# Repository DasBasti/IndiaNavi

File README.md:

# IndiaNavi
Offline Wandernavigation mit 7-Farben ePaper Display

## PCB
Board Version 2

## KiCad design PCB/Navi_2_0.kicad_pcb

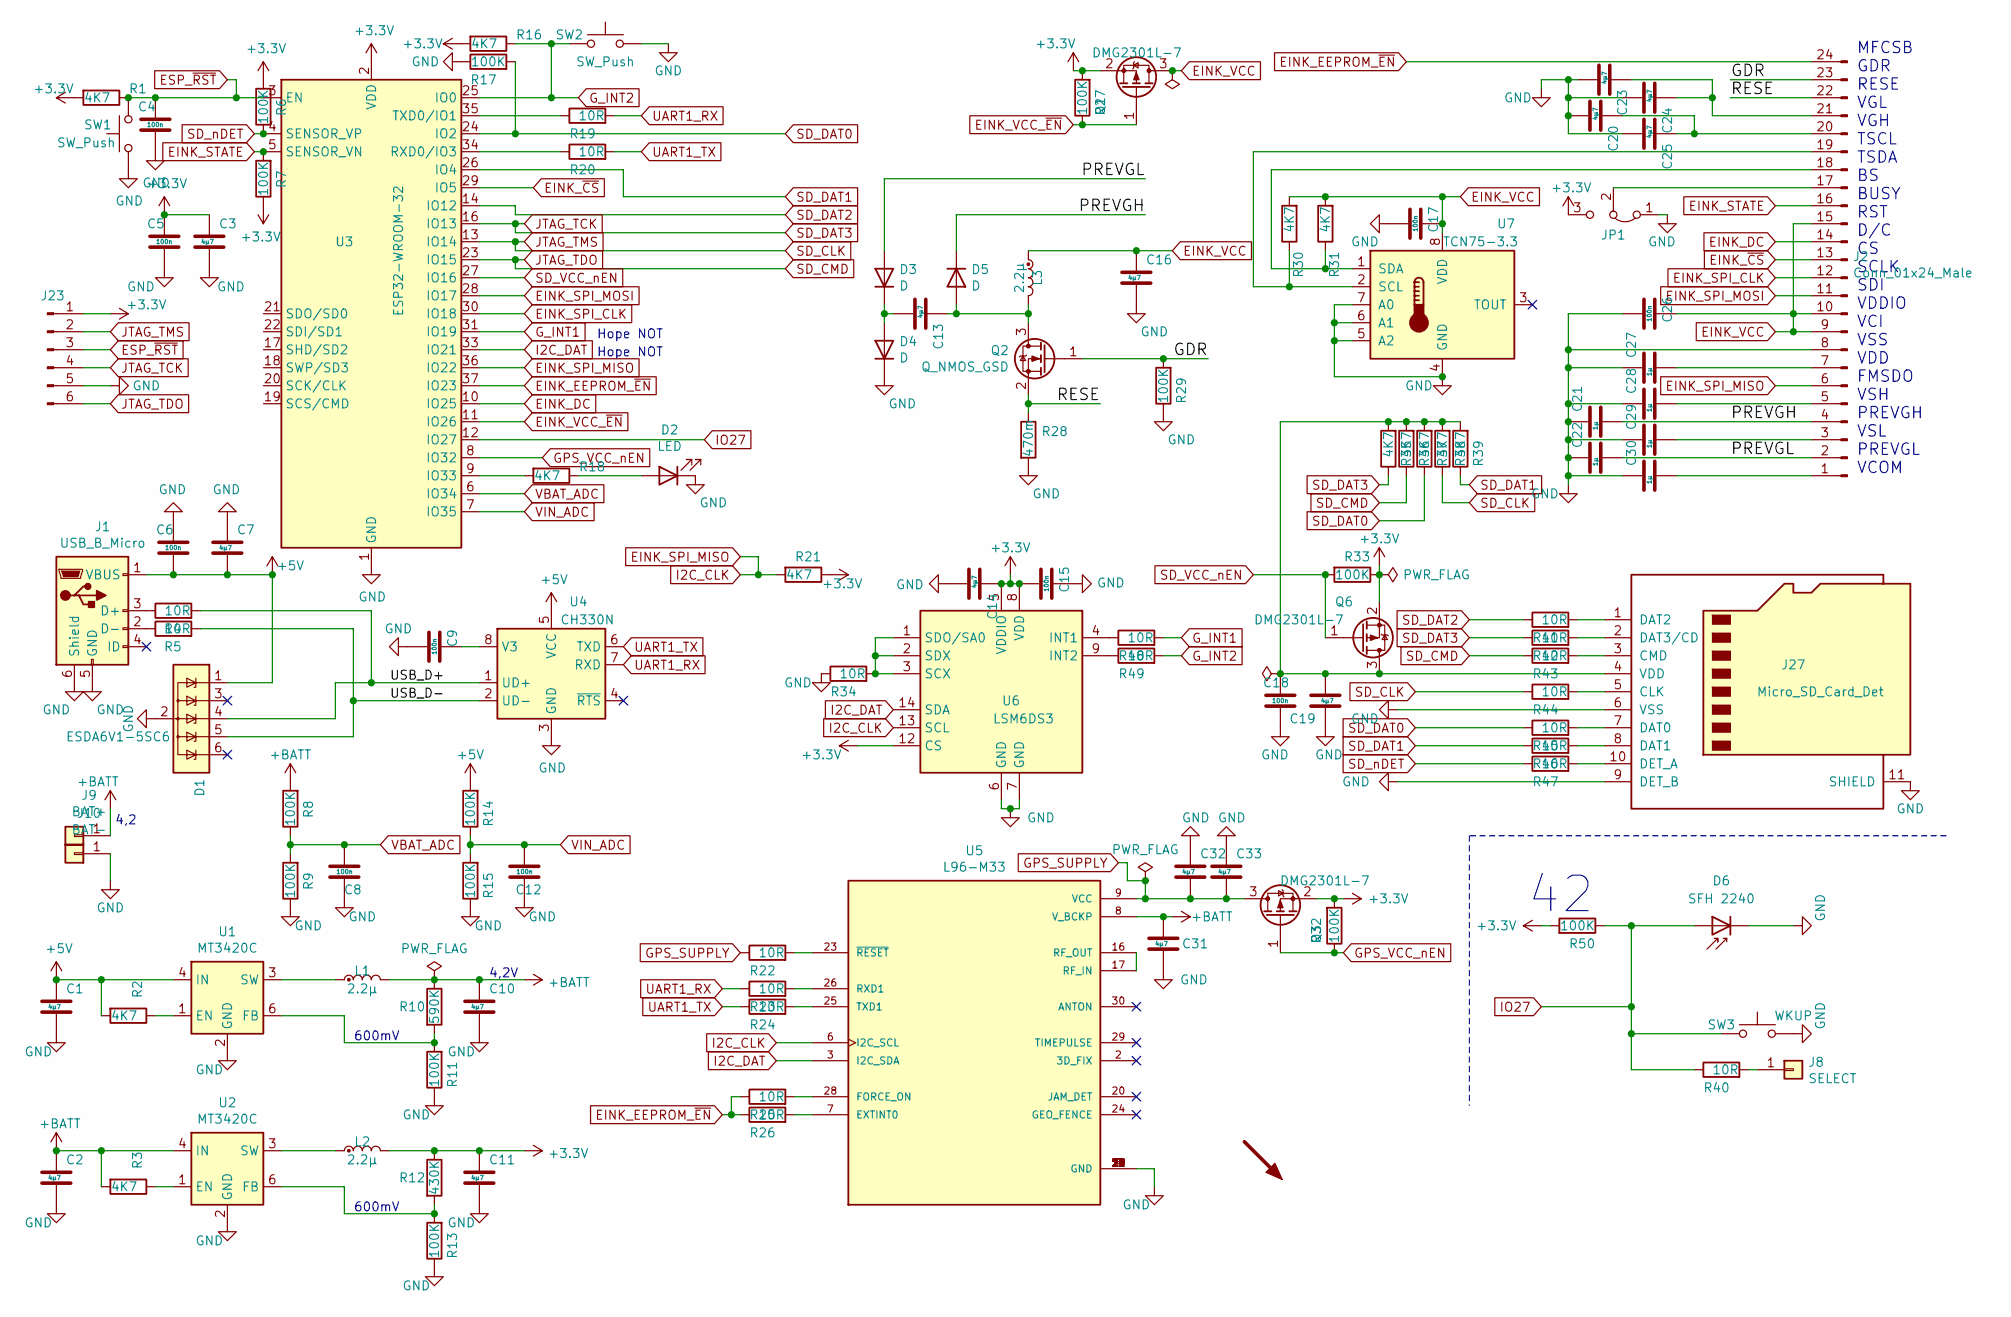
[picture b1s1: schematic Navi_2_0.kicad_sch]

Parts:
C1, C2, C3, C7, C10, C11, C13, C14, C16, C19, C20, C23, C24, C25, C31, C32, C33: 4µ7; C_0603_1608Metric; LCSC C307468
C4, C5, C6, C8, C9, C12, C15, C17, C18, C26: 100n; C_0603_1608Metric; LCSC C478888
C21, C22, C27, C28, C29, C30: 1µ; C_0603_1608Metric; LCSC C92796
D1: ESDA6V1-5SC6; SOT-23-6
D2: LED; LED_0603_1608Metric_Castellated; LCSC C965799
D3, D4, D5: D; D_SOD-123F; LCSC C383230
D6: SFH 2240; D_SMB
DISPLAY1: SYM_Arrow45_Large; EPD_MODUL 5.65
J1: USB_B_Micro; MICRO QTZB5.0; LCSC C2681556
J2: Conn_01x24_Male; Hirose_FH12-24S-0.5SH_1x24-1MP_P0.50mm_Horizontal
J8: SELECT; TestPoint_Pad_D1.0mm
J9: BAT+; TestPoint_Pad_D3.0mm
J10: BAT-; TestPoint_Pad_3.0x3.0mm
J23: Conn_01x06_Male; Tag-Connect_TC2030-IDC-NL_2x03_P1.27mm_Vertical
J27: Micro_SD_Card_Det; microSD_HC_Molex_104031-0811
JP1: Jumper_3_Bridged12; SolderJumper-3_P1.3mm_Bridged2Bar12_Pad1.0x1.5mm
L1, L2, L3: 2.2µ; L_1008_2520Metric_Pad1.43x2.20mm_HandSolder; LCSC C439320
Q1, Q3, Q6: DMG2301L-7; TSOT-23; LCSC C508195
Q2: Q_NMOS_GSD; SOT-23; LCSC C212304
R1, R16, R18, R21, R30, R31, R35, R36, R37, R38, R39: 4K7; R_0603_1608Metric; LCSC C105428
R2, R3: 4K7; R_0603_1608Metric
R4, R5, R19, R20, R22, R23, R24, R25, R26, R34, R40, R41, R42, R43, R44, R45, R46, R47, R48, R49: 10R; R_0603_1608Metric; LCSC C217691
R6, R7, R8, R9, R11, R13, R14, R15, R17, R27, R29, R32, R33, R50: 100K; R_0603_1608Metric; LCSC C15458
R10: 590K; R_0603_1608Metric
R12: 430K; R_0603_1608Metric
R28: 470m; R_0805_2012Metric; LCSC C270918
SW1: SW_Push; TS36CA
SW2: SW_Push; TS36CA; LCSC C412365
SW3: WKUP; SW_DIP_SPSTx01_Slide_6.7x4.1mm_W6.73mm_P2.54mm_LowProfile_J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; LCSC C412365
U1, U2: MT3420C; SOT-23-6
U3: ESP32-WROOM-32; LCSC C82899
U4: CH330N; SOIC-8_3.9x4.9mm_P1.27mm; LCSC C108996
U5: L96-M33; XCVR_L96-M33
U6: LSM6DS3; LGA-14_3x2.5mm_P0.5mm_LayoutBorder3x4y
U7: TCN75-3.3; SOIC-8_3.9x4.9mm_P1.27mm

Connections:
+3V3: C3.1, C5.1, C11.1, C14.1, C15.2, J23.1, JP1.3 (B), L2.2, Q1.2 (S), Q3.2 (S), Q6.2 (S), R1.2, R6.2, R7.1, R12.1, R16.2, R21.1, R27.2, R32.2, R33.1, R50.2, U3.2 (VDD), U6.5 (VDDIO), U6.8 (VDD), U6.12 (CS)
+5V: C1.1, C6.2, C7.2, D1.1 (IO1), J1.1 (VBUS), R2.2, R14.2, U1.4 (IN), U4.5 (VCC)
+BATT: C2.1, C10.1, C31.1, J9.1, L1.2, R3.2, R8.2, R10.1, U2.4 (IN), U5.8 (V_BCKP)
/GDR: J2.23, Q2.1 (G), R29.2
/PREVGH: C21.2, D5.1 (K), J2.4
/PREVGL: C22.2, D3.2 (A), J2.2
/RESE: J2.22, Q2.2 (S), R28.1
/USB_D+: D1.4 (IO3), R4.2, U4.1 (UD+)
/USB_D-: D1.5 (IO4), R5.2, U4.2 (UD-)
EINK_DC: J2.14, U3.10 (IO25)
EINK_EEPROM_~EN: J2.24, R25.1, R26.1, U3.37 (IO23)
EINK_SPI_CLK: J2.12, U3.30 (IO18)
EINK_SPI_MISO: J2.6, R21.2, U3.36 (IO22), U5.6 (I2C_SCL), U6.13 (SCL)
EINK_SPI_MOSI: J2.11, U3.28 (IO17)
EINK_STATE: J2.16, R7.2, U3.5 (SENSOR_VN)
EINK_VCC: C16.1, C17.1, C26.1, J2.9, J2.10, J2.15, L3.1, Q1.3 (D), R30.2, R31.2, U7.8 (VDD)
EINK_VCC_~EN: Q1.1 (G), R27.1, U3.11 (IO26)
EINK_~CS: J2.13, U3.29 (IO5)
ESP_~RST: C4.1, J23.3, R1.1, SW1.2, U3.3 (EN)
GND: C1.2, C2.2, C3.2, C4.2, C5.2, C6.1, C7.1, C8.1, C9.2, C10.2, C11.2, C12.1, C14.2, C15.1, C16.2, C17.2, C18.2, C19.1, C20.2, C21.1, C22.1, C23.2, C24.2, C25.2, C26.2, C27.1, C28.1, C29.1, C30.1, C31.2, C32.1, C33.1, D1.2 (GND), D2.1 (K), D4.1 (K), D6.1 (K), J1.5 (GND), J1.6 (Shield), J2.8, J10.1, J23.5, J27.6 (VSS), J27.9 (DET_B), J27.11 (SHIELD), JP1.1 (A), R9.1, R11.1, R13.1, R15.1, R17.1, R28.2, R29.1, R34.1, SW1.1, SW2.1, SW3.1, U1.2 (GND), U2.2 (GND), U3.1 (GND), U3.15 (GND), U3.38 (GND), U3.39 (GND), U4.3 (GND), U5.4 (GND), U5.5 (GND), U5.10 (GND), U5.11 (GND), U5.12 (GND), U5.13 (GND), U5.14 (GND), U5.15 (GND), U5.18 (GND), U5.19 (GND), U5.21 (GND), U5.22 (GND), U5.27 (GND), U5.31 (GND), U6.6 (GND), U6.7 (GND), U7.4 (GND), U7.5 (A2), U7.6 (A1), U7.7 (A0)
GPS_SUPPLY: C32.2, C33.2, Q3.3 (D), R22.1, U5.9 (VCC)
GPS_VCC_nEN: Q3.1 (G), R32.1, U3.8 (IO32)
G_INT1: R48.2, U3.31 (IO19)
G_INT2: R16.1, R49.2, SW2.2, U3.25 (IO0)
I2C_DAT: U3.33 (IO21), U5.3 (I2C_SDA), U6.14 (SDA)
IO27: D6.2 (A), R40.1, R50.1, SW3.2, U3.12 (IO27)
JTAG_TCK: J23.4, R35.1, R42.1, U3.16 (IO13)
JTAG_TDO: J23.6, R36.1, R43.1, U3.23 (IO15)
JTAG_TMS: J23.2, R38.1, R44.1, U3.13 (IO14)
unnamed: C9.1, U4.8 (V3)
unnamed: C13.1, D5.2 (A), L3.2, Q2.3 (D)
unnamed: C13.2, D3.1 (K), D4.2 (A)
unnamed: C18.1, C19.2, J27.4 (VDD), Q6.3 (D), R35.2, R36.2, R37.2, R38.2, R39.2
unnamed: C20.1, C25.1, J2.20
unnamed: C23.1, C24.1, J2.21
unnamed: C27.2, J2.7
unnamed: C28.2, J2.5
unnamed: C29.2, J2.3
unnamed: C30.2, J2.1
unnamed: D2.2 (A), R18.1
unnamed: J1.2 (D-), R5.1
unnamed: J1.3 (D+), R4.1
unnamed: J2.17, JP1.2 (C)
unnamed: J2.18, R31.1, U7.1 (SDA)
unnamed: J2.19, R30.1, U7.2 (SCL)
unnamed: J8.1, R40.2
unnamed: J27.1 (DAT2), R41.2
unnamed: J27.2 (DAT3/CD), R42.2
unnamed: J27.3 (CMD), R43.2
unnamed: J27.5 (CLK), R44.2
unnamed: J27.7 (DAT0), R45.2
unnamed: J27.8 (DAT1), R46.2
unnamed: J27.10 (DET_A), R47.2
unnamed: L1.1, U1.3 (SW)
unnamed: L2.1, U2.3 (SW)
unnamed: R2.1, U1.1 (EN)
unnamed: R3.1, U2.1 (EN)
unnamed: R10.2, R11.2, U1.6 (FB)
unnamed: R12.2, R13.2, U2.6 (FB)
unnamed: R18.2, U3.9 (IO33)
unnamed: R19.1, U3.35 (TXD0/IO1)
unnamed: R20.1, U3.34 (RXD0/IO3)
unnamed: R22.2, U5.23 (~RESET)
unnamed: R23.2, U5.26 (RXD1)
unnamed: R24.2, U5.25 (TXD1)
unnamed: R25.2, U5.28 (FORCE_ON)
unnamed: R26.2, U5.7 (EXTINT0)
unnamed: R34.2, U6.1 (SDO/SA0), U6.2 (SDX), U6.3 (SCX)
unnamed: U5.16 (RF_OUT), U5.17 (RF_IN)
unnamed: R48.1, U6.4 (INT1)
unnamed: R49.1, U6.9 (INT2)
SD_DAT0: R17.2, R37.1, R45.1, U3.24 (IO2)
SD_DAT1: R39.1, R46.1, U3.26 (IO4)
SD_DAT2: R41.1, U3.14 (IO12)
SD_VCC_nEN: Q6.1 (G), R33.2, U3.27 (IO16)
SD_nDET: R6.1, R47.1, U3.4 (SENSOR_VP)
UART1_RX: R19.2, R23.1, U4.7 (RXD)
UART1_TX: R20.2, R24.1, U4.6 (TXD)
VBAT_ADC: C8.2, R8.1, R9.2, U3.6 (IO34)
VIN_ADC: C12.2, R14.1, R15.2, U3.7 (IO35)
no_connect_(D1-Pad3): D1.3 (IO2)
no_connect_(D1-Pad6): D1.6 (IO5)
no_connect_(J1-Pad4): J1.4 (ID)
no_connect_(U1-Pad5): U1.5 (NC)
no_connect_(U2-Pad5): U2.5 (NC)
no_connect_(U3-Pad17): U3.17 (SHD/SD2)
no_connect_(U3-Pad18): U3.18 (SWP/SD3)
no_connect_(U3-Pad19): U3.19 (SCS/CMD)
no_connect_(U3-Pad20): U3.20 (SCK/CLK)
no_connect_(U3-Pad21): U3.21 (SDO/SD0)
no_connect_(U3-Pad22): U3.22 (SDI/SD1)
no_connect_(U3-Pad32): U3.32 (NC)
no_connect_(U4-Pad4): U4.4 (~RTS)
no_connect_(U5-Pad2): U5.2 (3D_FIX)
no_connect_(U5-Pad20): U5.20 (JAM_DET)
no_connect_(U5-Pad24): U5.24 (GEO_FENCE)
no_connect_(U5-Pad29): U5.29 (TIMEPULSE)
no_connect_(U5-Pad30): U5.30 (ANTON)
no_connect_(U6-Pad10): U6.10 (NC)
no_connect_(U6-Pad11): U6.11 (NC)
no_connect_(U7-Pad3): U7.3 (TOUT)

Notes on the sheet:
4,2
600mV
4,2V
Hope NOT
MFCSB GDR RESE VGL VGH TSCL TSDA BS BUSY RST D/C CS SCLK SDI VDDIO VCI VSS VDD FMSDO VSH PREVGH VSL PREVGL VCOM

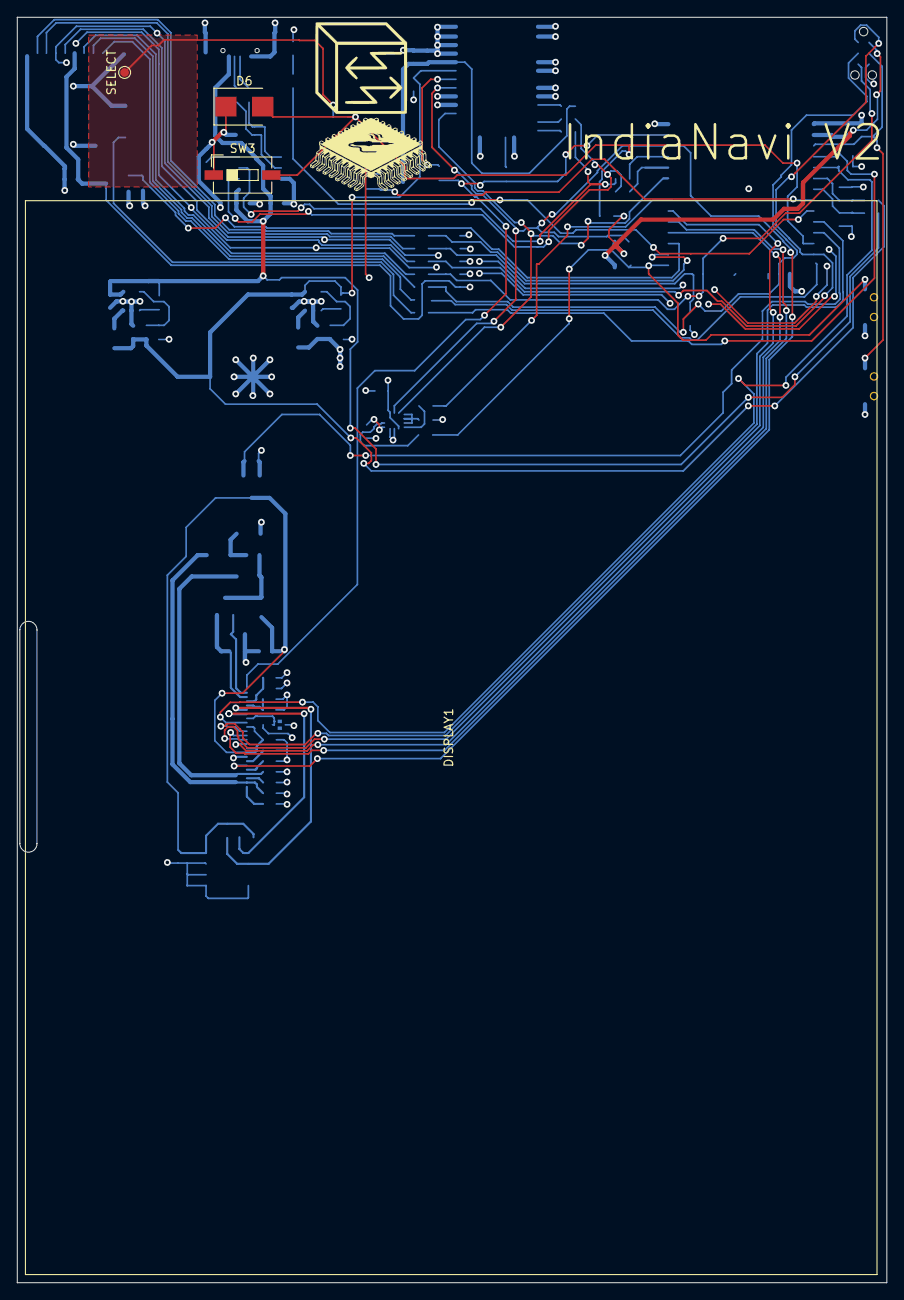
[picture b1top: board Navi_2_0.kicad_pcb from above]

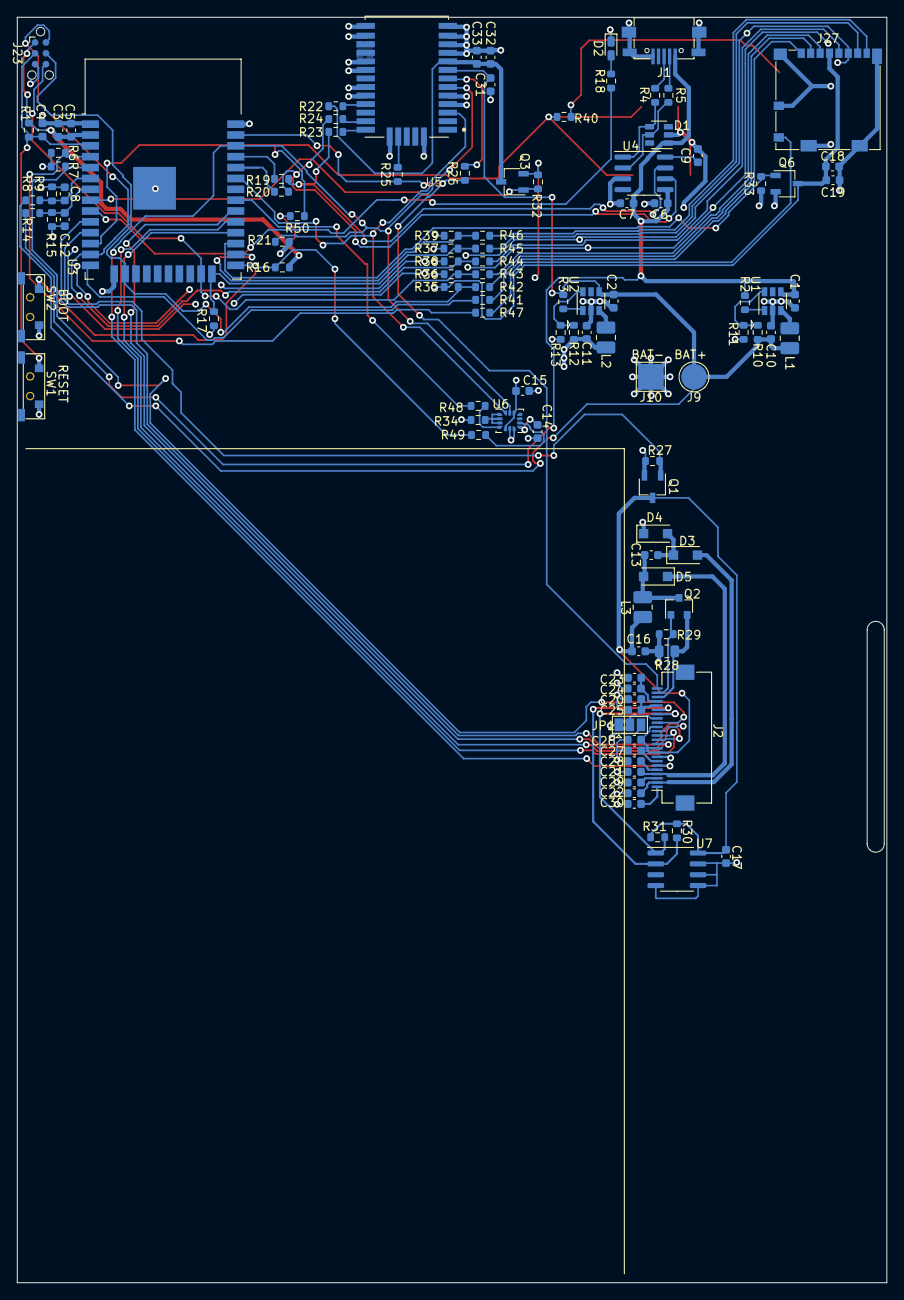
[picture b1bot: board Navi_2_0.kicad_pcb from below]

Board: 4 copper layers, 101.7 x 148.0 mm, 115 parts (111 on the bottom side), 80 nets.

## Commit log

2021-04-30 Version 2 initial commit
2021-05-06 Meeeeehr Widerstand
    Meeeeehr Widerstand (Test)
2021-05-20 remove PCB folder to add submodules
2021-05-20 Add PCB submodule
2021-05-20 Add CONVERTER submodule
2021-05-22 ADD: Firmware submodule
2021-05-22 rename submodule folder
2021-10-28 Update Repositories
2022-11-28 Update converter to opentopomap branch
